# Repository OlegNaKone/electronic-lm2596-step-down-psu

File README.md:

# electronic-lm2596-step-down-psu

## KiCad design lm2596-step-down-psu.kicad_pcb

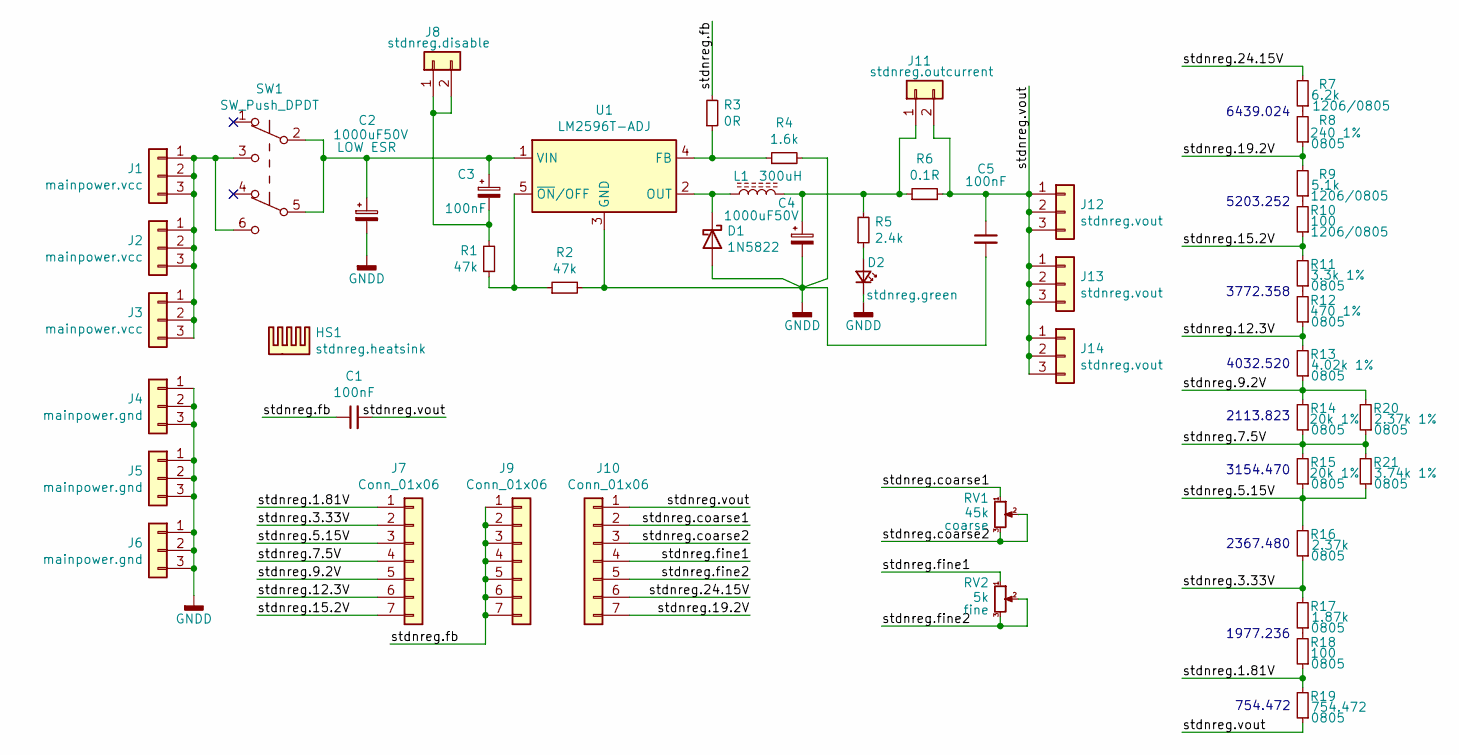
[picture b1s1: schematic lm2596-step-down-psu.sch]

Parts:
C1: 100nF; C_0805_2012Metric_Pad1.18x1.45mm_HandSolder
C2, C4: 1000uF50V; CP_Radial_D16.0mm_P7.50mm
C3, C5: 100nF; C_1206_3216Metric_Pad1.33x1.80mm_HandSolder
D1: 1N5822; D_DO-201AD_P12.70mm_Horizontal
D2: stdnreg.green; LED_D3.0mm
HS1: stdnreg.heatsink; Heatsink_16.36x16mm_2xFixation1.35mm
J1, J2, J3: mainpower.vcc; PinHeader_1x03_P2.54mm_Vertical
J4, J5, J6: mainpower.gnd; PinHeader_1x03_P2.54mm_Vertical
J7, J9, J10: Conn_01x06; PinHeader_1x07_P2.54mm_Vertical
J8: stdnreg.disable; PinHeader_1x02_P2.54mm_Vertical
J11: stdnreg.outcurrent; PinHeader_1x02_P2.54mm_Vertical
J12, J13, J14: stdnreg.vout; PinHeader_1x03_P2.54mm_Vertical
L1: 300uH; L_Toroid_Vertical_L16.0mm_W8.0mm_P7.62mm
R1, R2: 47k; R_1206_3216Metric_Pad1.30x1.75mm_HandSolder
R3: 0R; R_1206_3216Metric_Pad1.30x1.75mm_HandSolder
R4: 1.6k; R_1206_3216Metric_Pad1.30x1.75mm_HandSolder
R5: 2.4k; R_1206_3216Metric_Pad1.30x1.75mm_HandSolder
R6: 0.1R; R_2512_6332Metric_Pad1.40x3.35mm_HandSolder
R7: 6.2k; R_0805_2012Metric_Pad1.20x1.40mm_HandSolder
R8: 240 1%; R_0805_2012Metric_Pad1.20x1.40mm_HandSolder
R9: 5.1k; R_1206_3216Metric_Pad1.30x1.75mm_HandSolder
R10, R18: 100; R_0805_2012Metric_Pad1.20x1.40mm_HandSolder
R11: 3.3k 1%; R_0805_2012Metric_Pad1.20x1.40mm_HandSolder
R12: 470 1%; R_0805_2012Metric_Pad1.20x1.40mm_HandSolder
R13: 4.02k 1%; R_0805_2012Metric_Pad1.20x1.40mm_HandSolder
R14, R15: 20k 1%; R_0805_2012Metric_Pad1.20x1.40mm_HandSolder
R16: 2.37k; R_0805_2012Metric_Pad1.20x1.40mm_HandSolder
R17: 1.87k; R_0805_2012Metric_Pad1.20x1.40mm_HandSolder
R19: 754.472; R_0805_2012Metric_Pad1.20x1.40mm_HandSolder
R20: 2.37k 1%; R_0805_2012Metric_Pad1.20x1.40mm_HandSolder
R21: 3.74k 1%; R_0805_2012Metric_Pad1.20x1.40mm_HandSolder
RV1: 45k; Potentiometer_Bourns_3386C_Horizontal
RV2: 5k; Potentiometer_Bourns_3386C_Horizontal
SW1: SW_Push_DPDT; SW_Push_DPDT_8.4x8.4mm
U1: LM2596T-ADJ; TO-220-5_Vertical

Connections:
/stdnreg.1.81V: J7.1, R18.1, R19.2
/stdnreg.3.33V: J7.2, R16.1, R17.2
/stdnreg.5.15V: J7.3, R15.1, R16.2, R21.1
/stdnreg.7.5V: J7.4, R14.1, R15.2, R20.1, R21.2
/stdnreg.9.2V: J7.5, R13.1, R14.2, R20.2
/stdnreg.12.3V: J7.6, R12.1, R13.2
/stdnreg.15.2V: J7.7, R10.1, R11.2
/stdnreg.19.2V: J10.7, R8.1, R9.2
/stdnreg.24.15V: J10.6, R7.2
/stdnreg.coarse1: J10.2, RV1.1
/stdnreg.coarse2: J10.3, RV1.2, RV1.3
/stdnreg.fb: C1.1, J9.1, J9.2, J9.3, J9.4, J9.5, J9.6, J9.7, R3.2
/stdnreg.fine1: J10.4, RV2.1
/stdnreg.fine2: J10.5, RV2.2, RV2.3
/stdnreg.vout: C1.2, C5.1, J10.1, J11.2, J12.1, J12.2, J12.3, J13.1, J13.2, J13.3, J14.1, J14.2, J14.3, R6.2, R19.1
GNDD: C2.2, C4.2, C5.2, D1.2 (A), D2.1 (K), J4.1, J4.2, J4.3, J5.1, J5.2, J5.3, J6.1, J6.2, J6.3, R2.2, R4.2, U1.3 (GND)
unnamed: C2.1, C3.1, SW1.2 (B), SW1.5 (B), U1.1 (VIN)
unnamed: C3.2, J8.1, J8.2, R1.2
unnamed: C4.1, J11.1, L1.2, R5.2, R6.1
unnamed: D1.1 (K), L1.1, U1.2 (OUT)
unnamed: D2.2 (A), R5.1
unnamed: J1.1, J1.2, J1.3, J2.1, J2.2, J2.3, J3.1, J3.2, J3.3, SW1.3 (C), SW1.6 (C)
unnamed: R1.1, R2.1, U1.5 (~ON~/OFF)
unnamed: R3.1, R4.1, U1.4 (FB)
unnamed: R7.1, R8.2
unnamed: R9.1, R10.2
unnamed: R11.1, R12.2
unnamed: R17.1, R18.2

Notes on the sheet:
2113.823
4032.520
3772.358
5203.252
6439.024
2367.480
1977.236
754.472
3154.470

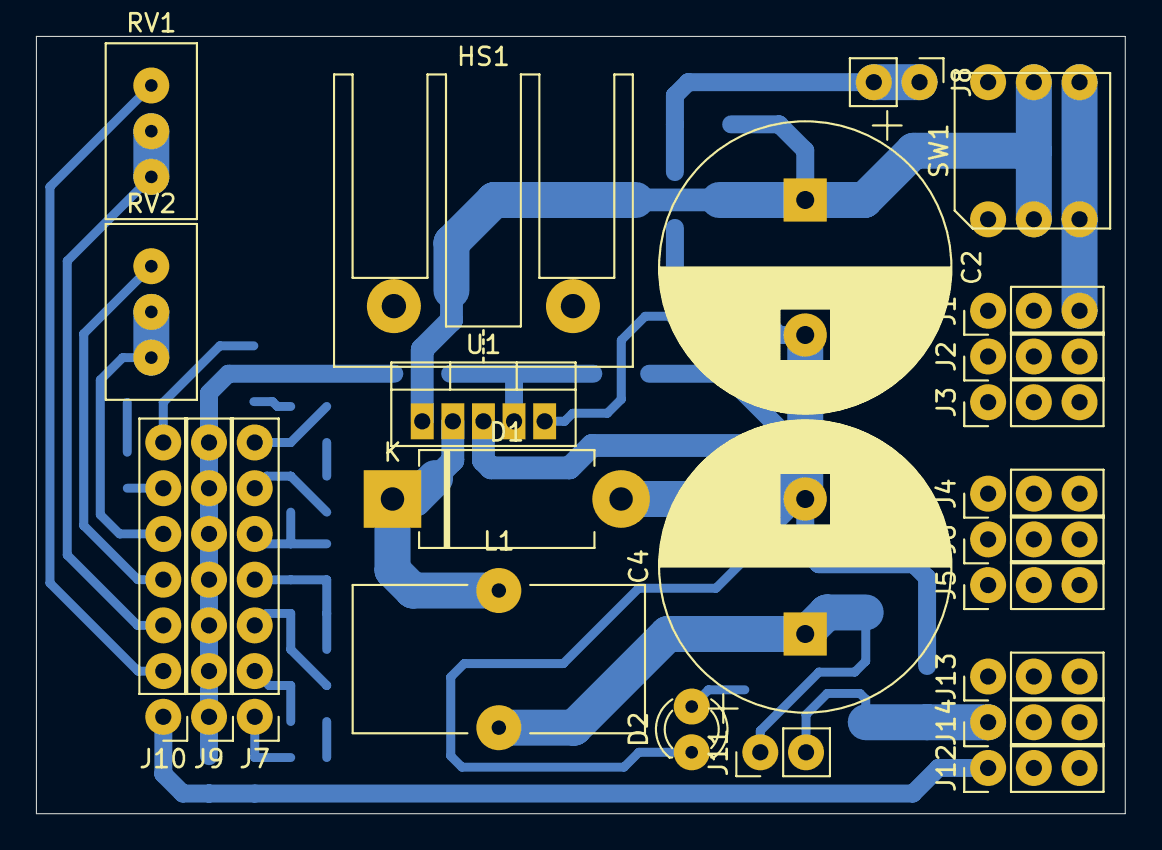
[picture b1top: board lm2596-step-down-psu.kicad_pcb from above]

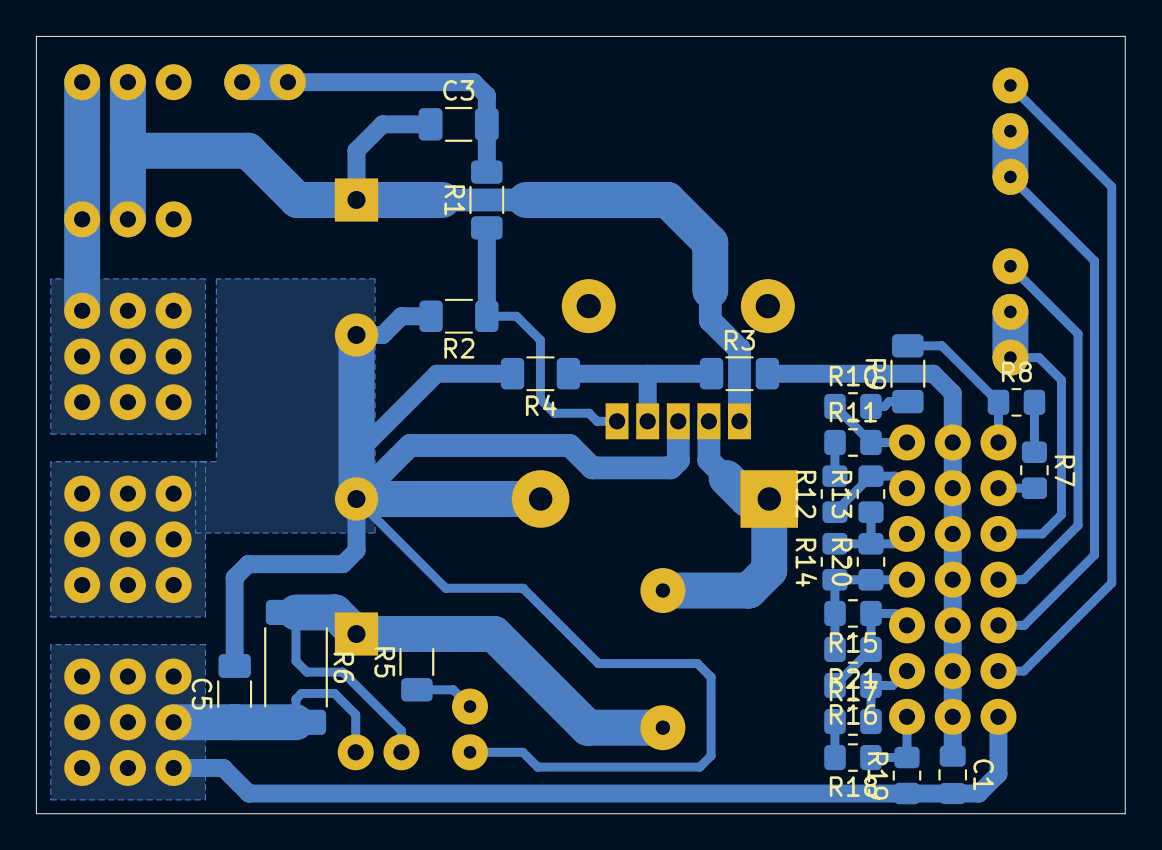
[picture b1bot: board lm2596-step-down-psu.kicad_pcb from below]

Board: 2 copper layers, 60.5 x 43.2 mm, 48 parts (24 on the bottom side), 28 nets.

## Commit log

2022-04-05 init
